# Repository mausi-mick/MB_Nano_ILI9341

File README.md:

.
    Test Board für Arduino „NANOs“ mit ILI9341, ILI9488-bzw. ST7735 SPI-Display

Bei vielen meiner Projekte  verwende ich den Arduino NANO oder Pin-kompatible Prozessoren mit dem TFT-Farb-Display ILI9341 bzw. ILI9488 bzw. ST7735 aus folgenden Gründen:
  
    • Existenz vieler Bibliotheken (libs) mit zahlreichen Beispielen für Prozessor und Display
    • kompaktes Board mit relativ grosser Anzahl herausgeführter Pins für andere Funktionen,
    • leicht beschaffbar / preisgünstig
    • Existenz von „NANO“  Boards mit anderem Processor mit NANO-“Pin-mapping“
    • mit HW-SPI ist das Display -auch am NANO – relativ schnell
    • die SPI-Displays ILI9341, ILI9488 und ST7735 haben gleiche/ähnliche Pinbelegung 
    • unterschiedliche Displaygrössen (1.8“,2,4“,2.8“,3.2“.3.5“,4“) (mit/ohne Touch) erhältlich
    • unterschiedliche Auflösungen (128x160), (240x320), (320x 400)

mittlerweile sind zum Arduino-NANO pinkompatible Boards erhältlich, z.B. :
  
    • LGT8F328P----»Mini EVB Nano style“, Prozessor: modifzierter ATMega328
    • Arduino EVERY:                                     Prozessor: ATMega4809
    • Arduino NANO ESP32                           ,Prozessor: ESP32
    • Arduino NANO 33 BLE                         ,Prozessor: nRF52840
    • Arduino NANO 33 IOT                         , Prozessor: M0+SAMD21
    • Arduino NANO RP2040 Connect          ,Prozessor: RP2040

Die neueren Boards sind dann eher auf 3,3 V Logik ausgerichtet bzw. z.T. umlötbar.

Als Entwickler möchte ich eigentlich möglichst schnell zur Anwendung kommen und mich nicht 
mit den Logik-Leveln rumschlagen , sondern den Prozessor und das Display auf ein
Board setzen und mit der Entwicklung loslegen., möglichst ohne viele Leitugen zu verlegen. 

Daher habe ich dieses Board entwickelt, auf dem Steckfassungen für das Display und das „NANO“-Board angeordnet sind und zusätzlich noch Steck Buchsen für:
    • einen DUAL-DAC MCP48x2
    • bis zu vier Drehencoder ( bzw. Potis),
    • vier Drucktaster
    • vier LED Anzeigen
    • ein Mini-Breadboard 
    • negative Sapnnungsquelle(-5V / ca 100mA) für Oper.verstärker

Das SPI-Display ( ILI9341, ILI9488, ST7735) wird direkt auf das Board gesteckt , auf dem sich die Verdrahtung für die Spannungsversorgung und die SPI-Anschlüsse (CS (Chipselect) an D10, DC (Data/Control) an D9)  des Displays befindet. Die Touch Pins und die SD-Karten Pins des Displays sind auf Buchsenleisten herausgeführt, ebenso wie alle Prozessor-Pins.

Es sind Displays in den Grössen 1.8“(ST7735), 2.4, 2.8 , 3.2“ (ILI9341) bzw. 3.5, 4.0“ (ILI9488) verwendbar.

Alles ist auf einer einlagigen Platine im Europa-Format (160x100) untergebracht.
Die Stromversorgung des Boards und die Programmierung erfolgt vom PC / Notebook über ein USB-Kabel, der Strom ist mit  500 mA abgesichert.
Ist die Programmierung abgeschlossen, kann das Board auch über eine USB Powerbank betrieben werden.

Nur für grössere Verbraucher (Servos, Motoren, Relais,…) wird eine zusätzliche entsprechend
dimensionierte Spannungsversorgung benötigt.

Von diesem „Main“ Board sind die „NANO“ Boards zur Programmierung über kurze USB Kabel verbunden, je nach Board mit Mini-USB (NANO), Micro-USB (Arduino EVERY, LTG8F328) oder
USB-C (LGT8F328 (blaue Platine),.

Zu dem Board gibt es KiCad-files (KiCad 7.0) und ein Blockdiagramm (DrawIO), auch als pdf.

Ausserdem gibt es noch zwei Adapter-Platinen für
den  
            Adafruit-Metro Mini 328
   
und den

            Raspberry PICO RP2040 (W) 
  Ausserdem werden Testprogramme zu den einzelnen Boards und Displays beigefügt.

   Hardware-Komponenten

hier sind jetzt nur die wesentlichen Komponenten / Module aufgeführt, die Details kann man den KiCad Stücklisten entnehmen.

    • ILI9341 SPI-Display (2.4“, 2.8“ oder 3.2“) (Touch bzw ohne Touch) (240x320 Pixel)
    • bzw ILI9488 Display (3,5“ bzw. 4.0“)  (Touch bzw ohne Touch) (320x400 Pixel)
    • bzw. ST7735 Display( 1.8“)  ohne Touch (128x160 Pixel)
    • Arduino NANO  oder Varianten gleicher Pin-Belegung 
    • USB C Buchse zur Verbindung PC/Notebbok
    • USB-A-Buchsezur Verbindung zum Prozesorboard
    • je nach Prozessorboard kurzes USB-Kabel mit mini-, micro USB-Stecker / USB-C-Stecker
    • diverse Buchsenleisten Raster 2.54 mm
    • LDO variabel ( MC33269) für 3.7V aus 5V
    • Schiebeschalter/Kippscahlter 1x UM)
    • diverse Widerstände, Kondenatoren ,  Dioden und Sicherungen
    • optional:
    •    DualDAC MCPM4802, MCP4812, MCP4822 ( 8, 10,12 bit SPI 
    •    1x DIL8-Fassung
    •    4xButtonSwitch
    •    4xLeds
    •    Dreh-Encoder (0-4 Stück)  ??
    •    Mini-Bread-Board
    •    -negatve Spannungsverorgung mit ICL7662 Modul
    •   Adapterboards für Adafruit Metro-Mini 328 / Raspberry PI RP2040

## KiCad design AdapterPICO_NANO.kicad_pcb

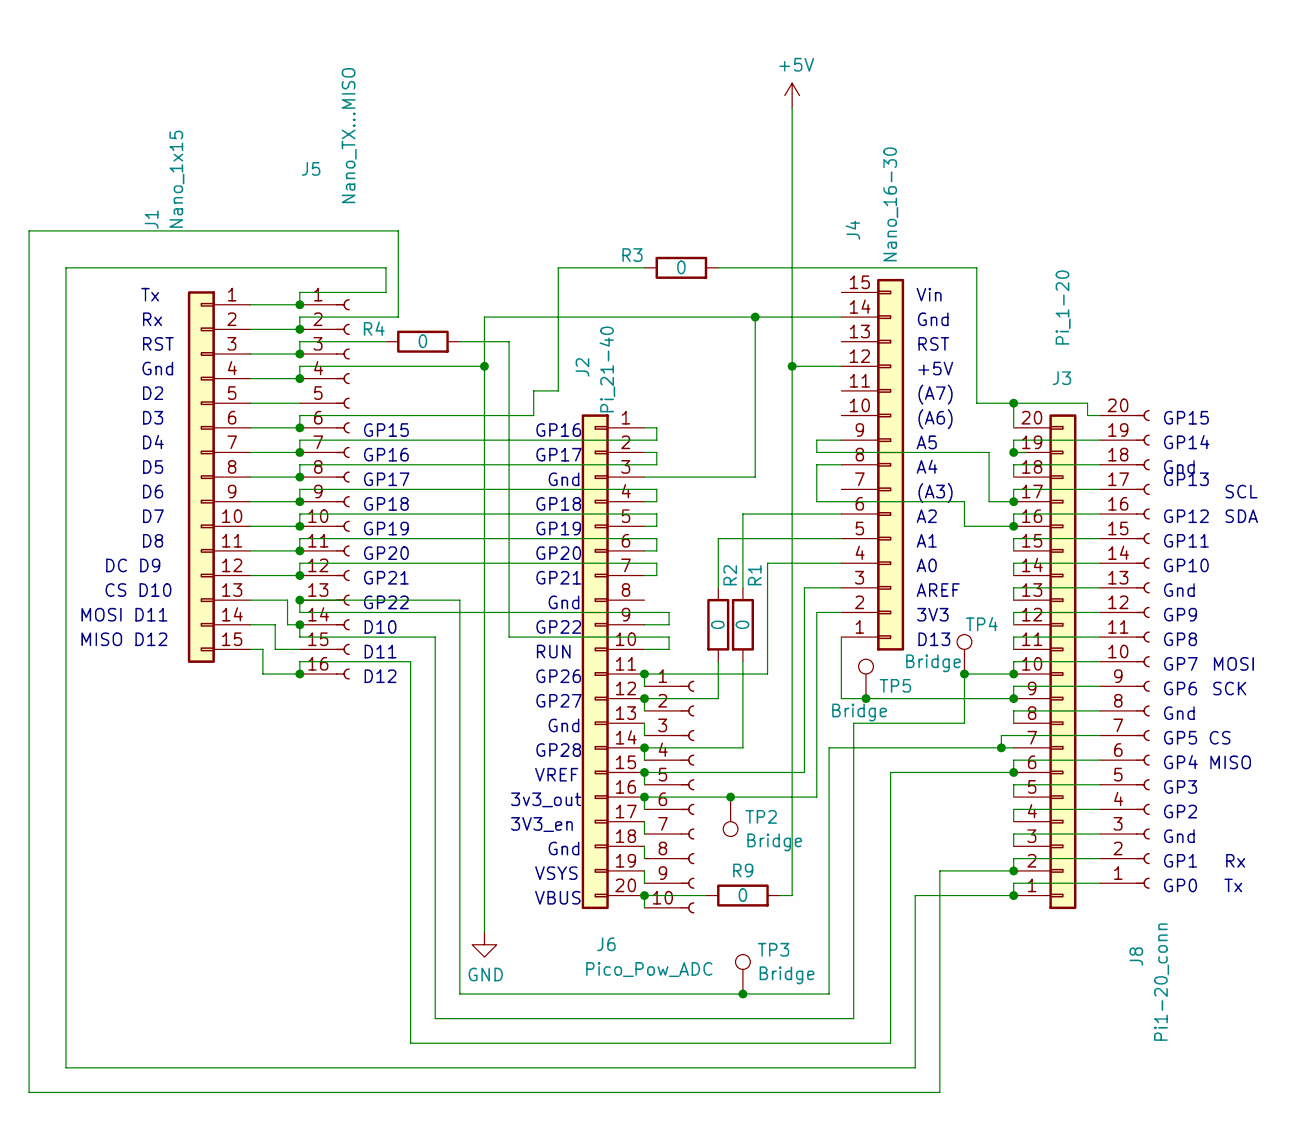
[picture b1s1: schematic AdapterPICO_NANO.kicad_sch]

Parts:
J1: Nano_1x15; PinHeader_1x15_P2.54mm_Vertical
J2: Pi_21-40; PinSocket_1x20_P2.54mm_Vertical
J3: Pi_1-20; PinSocket_1x20_P2.54mm_Vertical
J4: Nano_16-30; PinHeader_1x15_P2.54mm_Vertical
J5: Nano_TX...MISO; PinSocket_1x16_P2.54mm_Vertical
J6: Pico_Pow_ADC; PinSocket_1x10_P2.54mm_Vertical
J8: Pi1-20_conn; PinSocket_1x20_P2.54mm_Vertical
R1, R2, R3: 0; R_Axial_DIN0204_L3.6mm_D1.6mm_P7.62mm_Horizontal
R4: 0; R_Axial_DIN0207_L6.3mm_D2.5mm_P15.24mm_Horizontal
R9: 0; R_Axial_DIN0207_L6.3mm_D2.5mm_P10.16mm_Horizontal
TP2, TP3, TP4, TP5: Bridge; TestPoint_Bridge_Pitch5.08mm_Drill0.7mm

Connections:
+5V: J4.12, R9.2
GND: J1.4, J2.3, J4.14, J5.4
unnamed: J1.1, J3.1, J5.1, J8.1
unnamed: J1.2, J3.2, J5.2, J8.2
unnamed: J1.3, J5.3, R4.1
unnamed: J1.5, J5.5
unnamed: J1.6, J5.6, R3.1
unnamed: J1.7, J2.1, J5.7
unnamed: J1.8, J2.2, J5.8
unnamed: J1.9, J2.4, J5.9
unnamed: J1.10, J2.5, J5.10
unnamed: J1.11, J2.6, J5.11
unnamed: J1.12, J2.7, J5.12
unnamed: J1.13, J3.10, J5.14, J8.10, TP4.1
unnamed: J1.14, J5.15
unnamed: J1.15, J3.6, J5.16, J8.6
unnamed: J2.9, J3.7, J5.13, J8.7, TP3.1
unnamed: J2.10, R4.2
unnamed: J2.11, J4.4, J6.1
unnamed: J2.12, J6.2, R2.2
unnamed: J2.13, J6.3
unnamed: J2.14, J6.4, R1.2
unnamed: J2.15, J4.3, J6.5
unnamed: J2.16, J4.2, J6.6, TP2.1
unnamed: J2.17, J6.7
unnamed: J2.18, J6.8
unnamed: J2.19, J6.9
unnamed: J2.20, J6.10, R9.1
unnamed: J3.3, J8.3
unnamed: J3.4, J8.4
unnamed: J3.5, J8.5
unnamed: J3.8, J8.8
unnamed: J3.9, J4.1, J8.9, TP5.1
unnamed: J3.11, J8.11
unnamed: J3.12, J8.12
unnamed: J3.13, J8.13
unnamed: J3.14, J8.14
unnamed: J3.15, J8.15
unnamed: J3.16, J4.8, J8.16
unnamed: J3.17, J4.9, J8.17
unnamed: J3.18, J8.18
unnamed: J3.19, J8.19
unnamed: J3.20, J8.20, R3.2
unnamed: J4.5, R2.1
unnamed: J4.6, R1.1

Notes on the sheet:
D10
Vin
GP26
SDA
GP16
GP12
GP13
RST
GP9
VBUS
GP5 CS
CS D10
SCL
MOSI
GP20
GP7
3V3
DC D9
Gnd
GP15
GP3
(A6)
MISO D12
GP19
GP27
GP18
VSYS
D11
GP21
GP14
D12
SCK
(A3)
GP11
AREF
GP17
GP28
GP0
MOSI D11
RUN

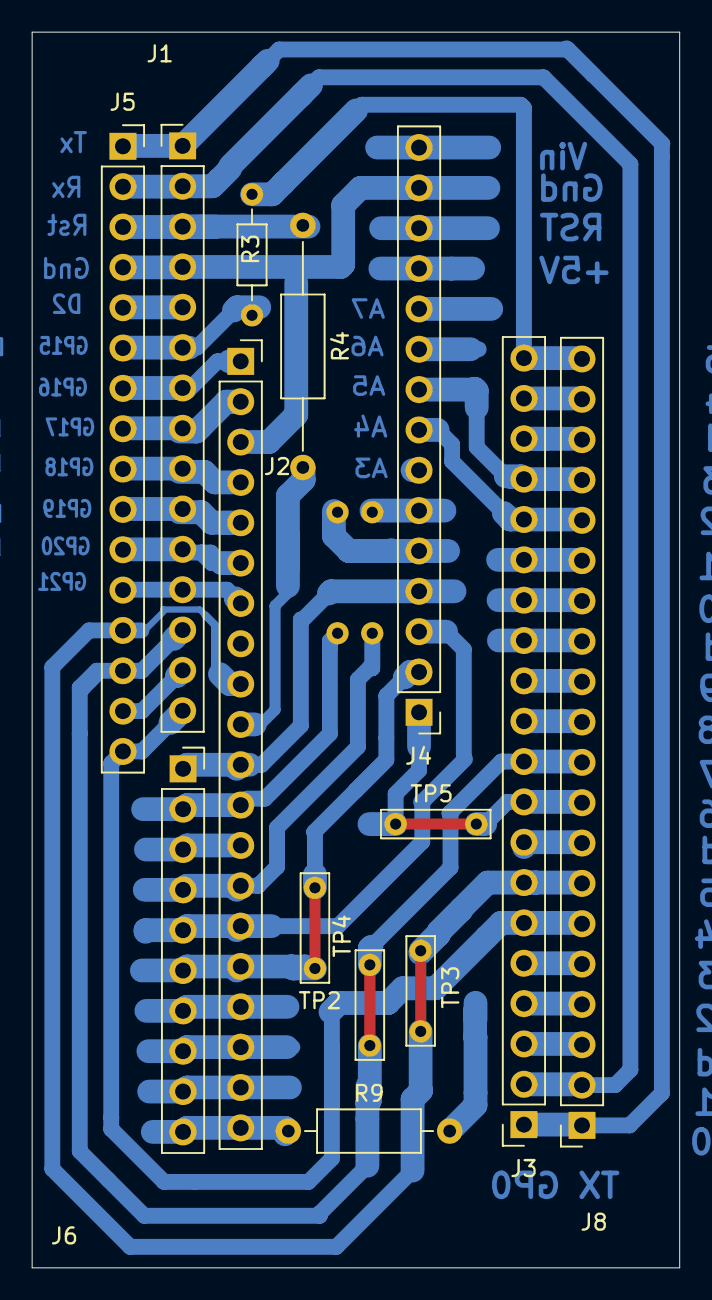
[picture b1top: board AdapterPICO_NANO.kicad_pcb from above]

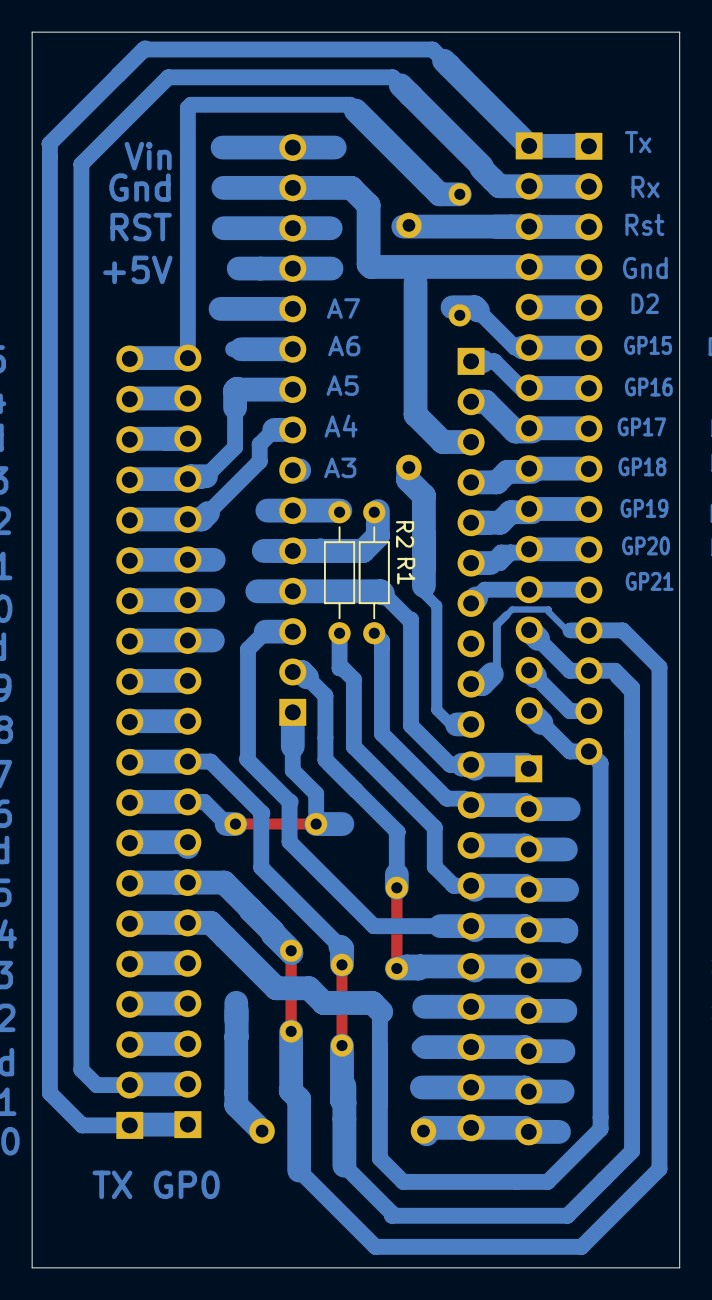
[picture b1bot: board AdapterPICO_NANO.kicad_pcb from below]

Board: 2 copper layers, 40.8 x 77.8 mm, 16 parts (2 on the bottom side), 45 nets.

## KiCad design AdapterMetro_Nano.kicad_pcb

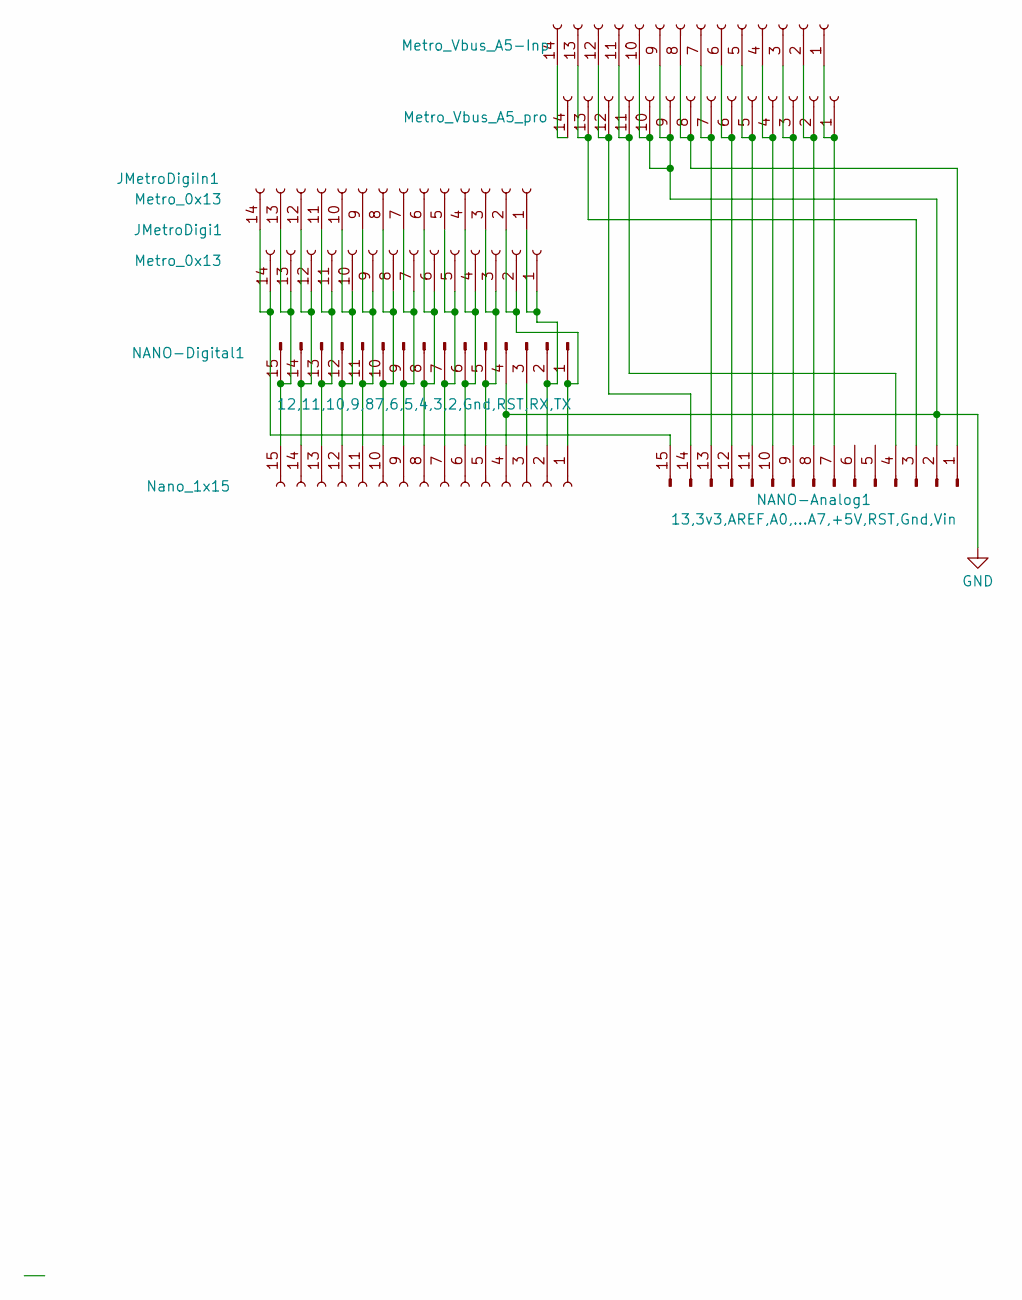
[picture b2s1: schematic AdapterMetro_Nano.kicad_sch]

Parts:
JMetroAna1: Metro_Vbus_A5-Inp; PinSocket_1x14_P2.54mm_Vertical
JMetroAna2: Metro_Vbus_A5_pro; PinSocket_1x14_P2.54mm_Vertical
JMetroDigi1: Metro_0x13; PinSocket_1x14_P2.54mm_Vertical
JMetroDigiIn1: Metro_0x13; PinSocket_1x14_P2.54mm_Vertical
JNanoDigi2: Nano_1x15; PinSocket_1x15_P2.54mm_Vertical
NANO-Analog1: 13,3v3,AREF,A0,...A7,+5V,RST,Gnd,Vin; PinHeader_1x15_P2.54mm_Vertical
NANO-Digital1: 12,11,10,9,87,6,5,4,3,2,Gnd,RST,RX,TX; PinHeader_1x15_P2.54mm_Vertical

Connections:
GND: JMetroAna1.9, JMetroAna1.10, JMetroAna2.9, JMetroAna2.10, JNanoDigi2.4, NANO-Analog1.2, NANO-Digital1.4
unnamed: JMetroAna1.1, JMetroAna2.1, NANO-Analog1.7
unnamed: JMetroAna1.2, JMetroAna2.2, NANO-Analog1.8
unnamed: JMetroAna1.3, JMetroAna2.3, NANO-Analog1.9
unnamed: JMetroAna1.4, JMetroAna2.4, NANO-Analog1.10
unnamed: JMetroAna1.5, JMetroAna2.5, NANO-Analog1.11
unnamed: JMetroAna1.6, JMetroAna2.6, NANO-Analog1.12
unnamed: JMetroAna1.7, JMetroAna2.7, NANO-Analog1.13
unnamed: JMetroAna1.8, JMetroAna2.8, NANO-Analog1.1
unnamed: JMetroAna1.11, JMetroAna2.11, NANO-Analog1.4
unnamed: JMetroAna1.12, JMetroAna2.12, NANO-Analog1.14
unnamed: JMetroAna1.13, JMetroAna2.13, NANO-Analog1.3
unnamed: JMetroAna1.14, JMetroAna2.14
unnamed: JMetroDigi1.1, JMetroDigiIn1.1, JNanoDigi2.2, NANO-Digital1.2
unnamed: JMetroDigi1.2, JMetroDigiIn1.2, JNanoDigi2.1, NANO-Digital1.1
unnamed: JMetroDigi1.3, JMetroDigiIn1.3, JNanoDigi2.5, NANO-Digital1.5
unnamed: JMetroDigi1.4, JMetroDigiIn1.4, JNanoDigi2.6, NANO-Digital1.6
unnamed: JMetroDigi1.5, JMetroDigiIn1.5, JNanoDigi2.7, NANO-Digital1.7
unnamed: JMetroDigi1.6, JMetroDigiIn1.6, JNanoDigi2.8, NANO-Digital1.8
unnamed: JMetroDigi1.7, JMetroDigiIn1.7, JNanoDigi2.9, NANO-Digital1.9
unnamed: JMetroDigi1.8, JMetroDigiIn1.8, JNanoDigi2.10, NANO-Digital1.10
unnamed: JMetroDigi1.9, JMetroDigiIn1.9, JNanoDigi2.11, NANO-Digital1.11
unnamed: JMetroDigi1.10, JMetroDigiIn1.10, JNanoDigi2.12, NANO-Digital1.12
unnamed: JMetroDigi1.11, JMetroDigiIn1.11, JNanoDigi2.13, NANO-Digital1.13
unnamed: JMetroDigi1.12, JMetroDigiIn1.12, JNanoDigi2.14, NANO-Digital1.14
unnamed: JMetroDigi1.13, JMetroDigiIn1.13, JNanoDigi2.15, NANO-Digital1.15
unnamed: JMetroDigi1.14, JMetroDigiIn1.14, NANO-Analog1.15
unnamed: JNanoDigi2.3, NANO-Digital1.3

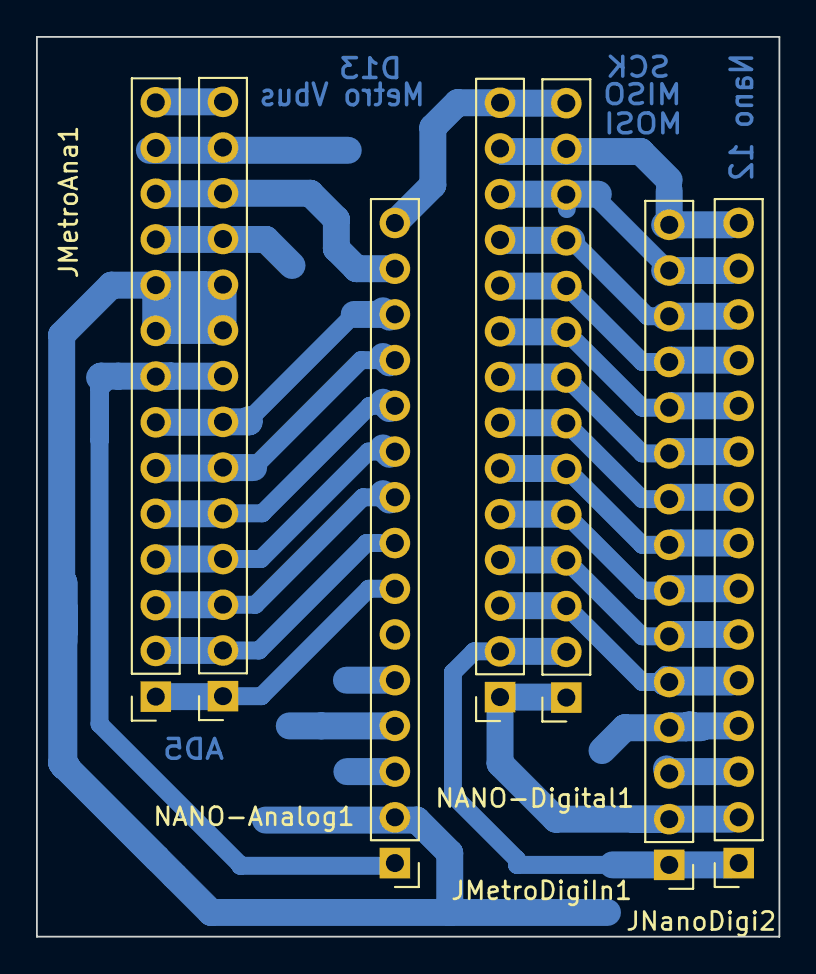
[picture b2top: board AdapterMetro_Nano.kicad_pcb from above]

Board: 2 copper layers, 41.2 x 50.0 mm, 7 parts (0 on the bottom side), 28 nets.

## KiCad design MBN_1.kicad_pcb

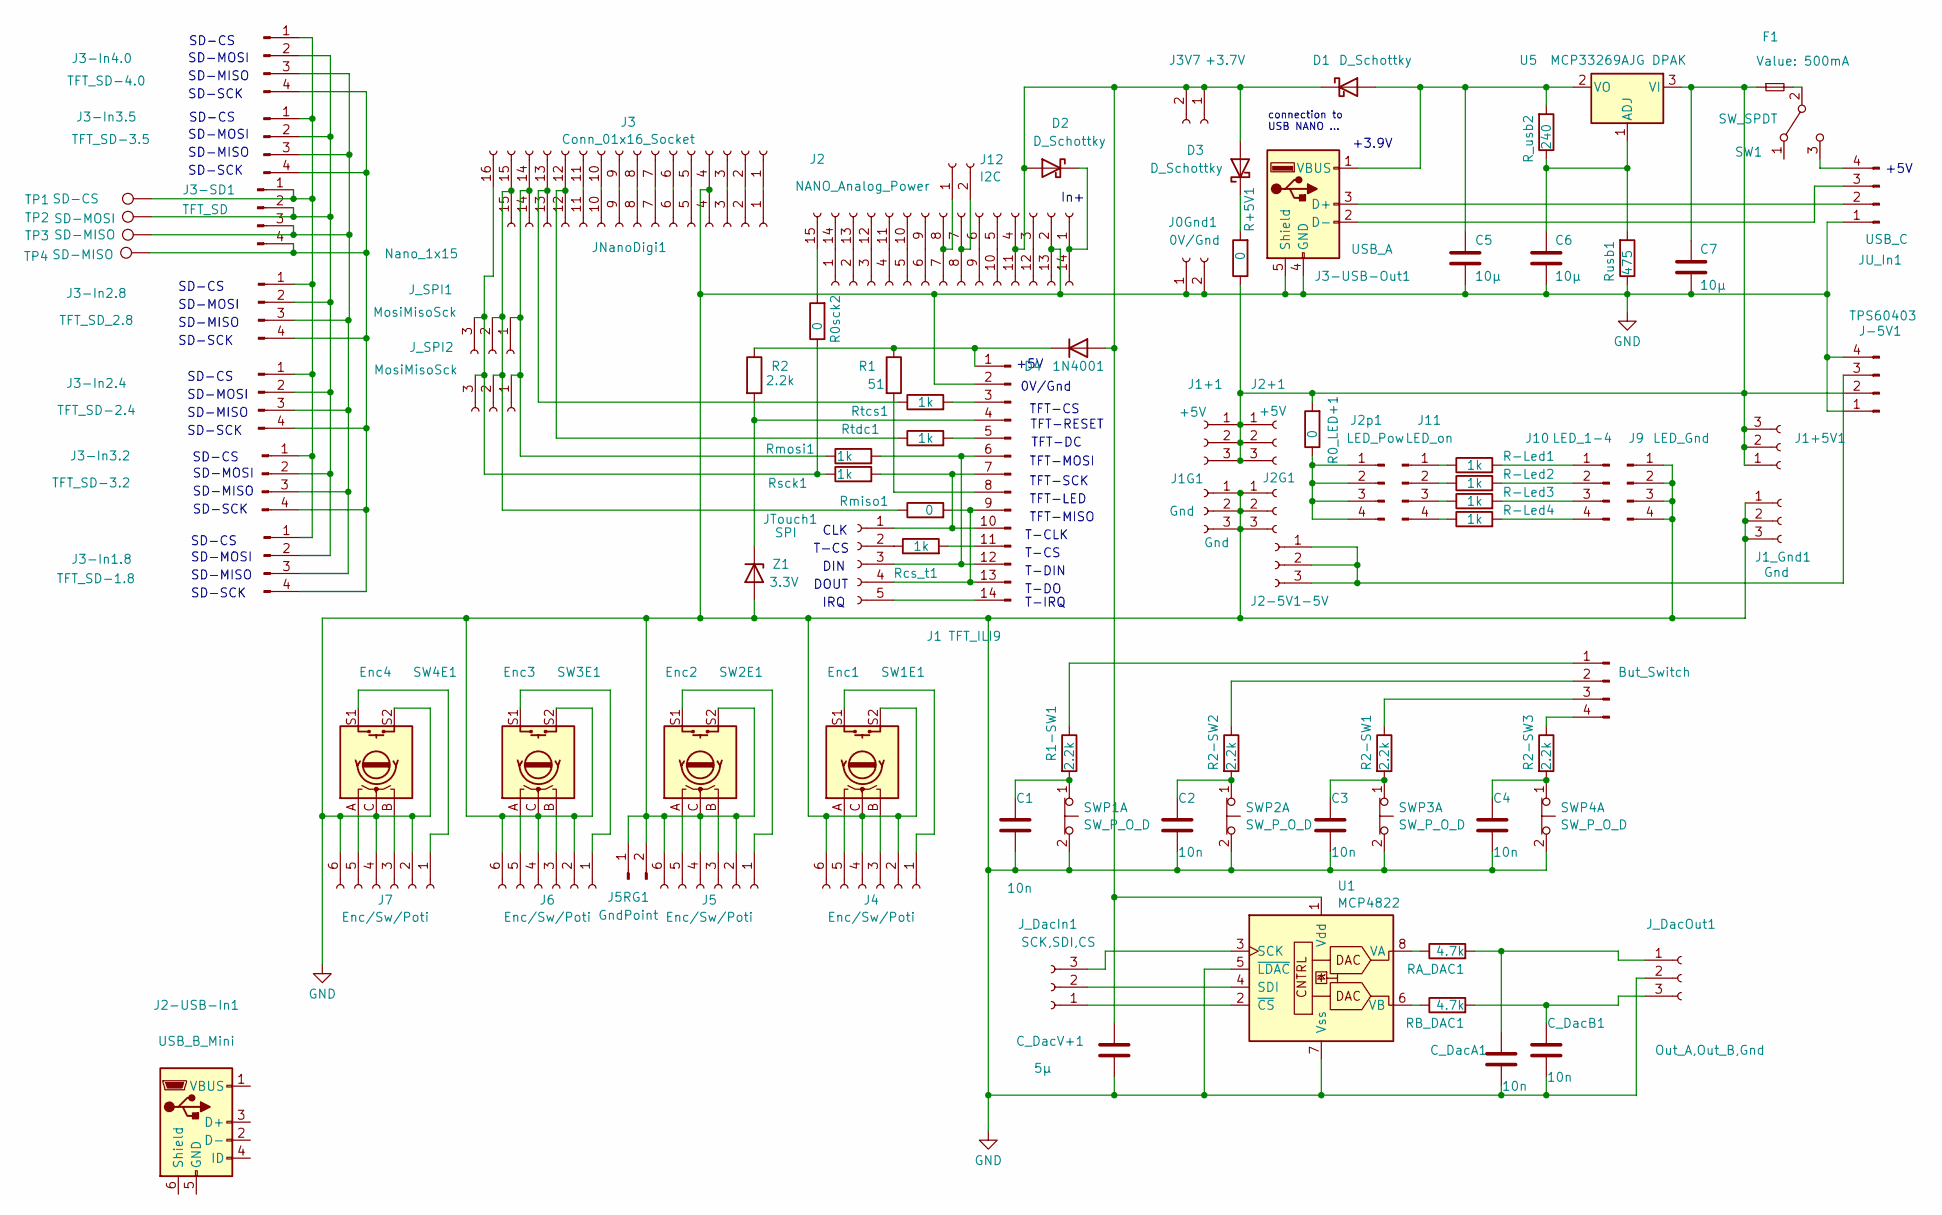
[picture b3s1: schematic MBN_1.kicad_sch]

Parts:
C1, C2, C3, C4: 10n; C_1206_3216Metric_Pad1.33x1.80mm_HandSolder
C5, C6, C7: 10µ; C_1812_4532Metric_Pad1.57x3.40mm_HandSolder
C_DacA1: 10n; C_1206_3216Metric_Pad1.33x1.80mm_HandSolder
C_DacB1: 10n; C_1206_3216Metric_Pad1.33x1.80mm_HandSolder
C_DacV+1: 5µ; C_1812_4532Metric_Pad1.57x3.40mm_HandSolder
D1: D_Schottky; D_DO-15_P15.24mm_Horizontal
D2: D_Schottky; D_2010_5025Metric_Pad1.52x2.65mm_HandSolder
D3: D_Schottky; D_DO-15_P12.70mm_Horizontal
D4: 1N4001; D_2010_5025Metric_Pad1.52x2.65mm_HandSolder
F1: 500mA; Fuse_2010_5025Metric_Pad1.52x2.65mm_HandSolder
J0Gnd1: 0V/Gnd; PinHeader_1x02_P2.54mm_Vertical
J1: TFT_ILI9; PinHeader_1x14_P2.54mm_Vertical
J1+1, J1+5V1, J2+1: +5V; PinHeader_1x03_P2.54mm_Vertical
J1G1, J1_Gnd1, J2G1: Gnd; PinHeader_1x03_P2.54mm_Vertical
J2: NANO_Analog_Power; PinHeader_1x14_P2.54mm_Vertical
J2-5V1: -5V; PinHeader_1x03_P2.54mm_Vertical
J2-USB-In1: USB_B_Mini; USB_Mini-B_Wuerth_65100516121_Horizontal
J2p1: LED_Pow; PinHeader_1x04_P2.54mm_Vertical
J3: Conn_01x16_Socket; PinHeader_1x16_P2.54mm_Vertical
J3-In1.8: TFT_SD-1.8; PinHeader_1x04_P2.54mm_Vertical
J3-In2.4: TFT_SD-2.4; PinHeader_1x04_P2.54mm_Vertical
J3-In2.8: TFT_SD_2.8; PinSocket_1x04_P2.54mm_Vertical
J3-In3.2: TFT_SD-3.2; PinHeader_1x04_P2.54mm_Vertical
J3-In3.5: TFT_SD-3.5; PinHeader_1x04_P2.54mm_Vertical
J3-In4.0: TFT_SD-4.0; PinHeader_1x04_P2.54mm_Vertical
J3-SD1: TFT_SD; PinHeader_1x04_P2.54mm_Horizontal
J3-USB-Out1: USB_A; USB_A_Stewart_SS-52100-001_Horizontal
J3V7: +3.7V; PinHeader_1x02_P2.54mm_Vertical
J4, J5, J6, J7: Enc/Sw/Poti; PinHeader_1x06_P2.54mm_Vertical
J5RG1: GndPoint; PinHeader_1x02_P2.54mm_Vertical
J8: But_Switch; PinHeader_1x04_P2.54mm_Vertical
J9: LED_Gnd; PinHeader_1x04_P2.54mm_Vertical
J10: LED_1-4; PinHeader_1x04_P2.54mm_Vertical
J11: LED_on; PinHeader_1x04_P2.54mm_Vertical
J12: I2C; PinHeader_1x02_P2.54mm_Vertical
J-5V1: TPS60403; PinHeader_1x04_P2.54mm_Vertical
JNanoAnal_1_15: +InGnd...; PinSocket_1x15_P2.54mm_Vertical
JNanoDigi1: Nano_1x15; PinSocket_1x15_P2.54mm_Vertical
JTouch1: SPI; PinHeader_1x05_P2.54mm_Vertical
JU_In1: USB_C; PinHeader_1x04_P2.54mm_Vertical
J_DacIn1: SCK,SDI,CS; PinHeader_1x03_P2.54mm_Vertical
J_DacOut1: Out_A,Out_B,Gnd; PinHeader_1x03_P2.54mm_Vertical
J_SPI1, J_SPI2: MosiMisoSck; PinHeader_1x03_P2.54mm_Vertical
R0_LED+1, R0sck2: 0; R_Axial_DIN0207_L6.3mm_D2.5mm_P15.24mm_Horizontal
R1: 51; R_Axial_DIN0309_L9.0mm_D3.2mm_P20.32mm_Horizontal
R1-SW1, R2-SW1, R2-SW2, R2-SW3: 2.2k; R_1206_3216Metric_Pad1.30x1.75mm_HandSolder
R2: 2.2k; R_Axial_DIN0207_L6.3mm_D2.5mm_P10.16mm_Horizontal
R+5V1: 0; R_Axial_DIN0207_L6.3mm_D2.5mm_P10.16mm_Horizontal
R-Led1, R-Led2, R-Led3, R-Led4: 1k; R_1206_3216Metric_Pad1.30x1.75mm_HandSolder
RA_DAC1: 4.7k; R_1206_3216Metric_Pad1.30x1.75mm_HandSolder
RB_DAC1: 4.7k; R_1206_3216Metric_Pad1.30x1.75mm_HandSolder
R_usb2: 240; R_Axial_DIN0207_L6.3mm_D2.5mm_P10.16mm_Horizontal
Rcs_t1: 1k; R_0805_2012Metric_Pad1.20x1.40mm_HandSolder
Rmiso1: 0; R_Axial_DIN0207_L6.3mm_D2.5mm_P10.16mm_Horizontal
Rmosi1: 1k; R_Axial_DIN0204_L3.6mm_D1.6mm_P7.62mm_Horizontal
Rsck1: 1k; R_Axial_DIN0207_L6.3mm_D2.5mm_P15.24mm_Horizontal
Rtcs1: 1k; R_0805_2012Metric_Pad1.20x1.40mm_HandSolder
Rtdc1: 1k; R_0805_2012Metric_Pad1.20x1.40mm_HandSolder
Rusb1: 475; R_Axial_DIN0207_L6.3mm_D2.5mm_P10.16mm_Horizontal
SW1: SW_SPDT; Molex_KK-396_5273-03A_1x03_P3.96mm_Vertical
SW1E1: Enc1; RotaryEncoder_Alps_EC11E-Switch_Vertical_H20mm
SW2E1: Enc2; RotaryEncoder_Alps_EC11E-Switch_Vertical_H20mm
SW3E1: Enc3; RotaryEncoder_Alps_EC11E-Switch_Vertical_H20mm
SW4E1: Enc4; RotaryEncoder_Alps_EC11E-Switch_Vertical_H20mm
SWP1, SWP2, SWP3, SWP4: SW_P_O_D; SW_PUSH_6mm_H7.3mm
TP1: SD-CS; TestPoint_Keystone_5000-5004_Miniature
TP2: SD-MOSI; TestPoint_Keystone_5000-5004_Miniature
TP3, TP4: SD-MISO; TestPoint_Keystone_5000-5004_Miniature
U1: MCP4822; DIP-8_W7.62mm_LongPads
U5: MCP33269AJG DPAK; ATPAK-2
Z1: 3.3V; D_DO-41_SOD81_P7.62mm_Horizontal

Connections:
GND: C1.2, C2.2, C3.2, C4.2, C5.2, C6.2, C7.2, C_DacA1.2, C_DacB1.2, C_DacV+1.2, J0Gnd1.1, J0Gnd1.2, J1.2, J1G1.1, J1G1.2, J1G1.3, J1_Gnd1.1, J1_Gnd1.2, J1_Gnd1.3, J2.13, J2G1.1, J2G1.2, J2G1.3, J3.4, J3-USB-Out1.4 (GND), J3-USB-Out1.5 (Shield), J4.2, J4.4, J4.6, J5.2, J5.4, J5.6, J5RG1.1, J5RG1.2, J6.2, J6.4, J6.6, J7.2, J7.4, J7.6, J9.1, J9.2, J9.3, J9.4, J-5V1.1, J-5V1.4, JNanoAnal_1_15.2, JNanoDigi1.4, JU_In1.1, J_DacOut1.2, Rusb1.1, SW1E1.C, SW1E1.S2, SW2E1.C, SW2E1.S2, SW3E1.C, SW3E1.S2, SW4E1.C, SW4E1.S2, SWP1.2, SWP2.2, SWP3.2, SWP4.2, U1.5 (~LDAC), U1.7 (Vss), Z1.2 (A)
unnamed: C1.1, R1-SW1.2, SWP1.1
unnamed: C2.1, R2-SW2.2, SWP2.1
unnamed: C3.1, R2-SW1.2, SWP3.1
unnamed: C4.1, R2-SW3.2, SWP4.1
unnamed: C5.1, D1.2 (A), J3-USB-Out1.1 (VBUS), R_usb2.2, U5.2 (VO)
unnamed: C_DacV+1.1, D1.1 (K), D2.2 (A), D3.2 (A), D4.2 (A), J2.11, J3V7.1, J3V7.2, JNanoAnal_1_15.4, U1.1 (Vdd)
unnamed: D2.1 (K), J2.14, JNanoAnal_1_15.1
unnamed: D3.1 (K), R+5V1.2
unnamed: D4.1 (K), J1.1, R1.1, R2.1
unnamed: J1.3, Rtcs1.2
unnamed: J1.4, R2.2, Z1.1 (K)
unnamed: J1.5, Rtdc1.2
unnamed: J1.8, R1.2
unnamed: J1.7, J1.10, JTouch1.1, Rsck1.2
unnamed: J1.11, Rcs_t1.2
unnamed: J1.6, J1.12, JTouch1.3, Rmosi1.2
unnamed: J1.9, J1.13, JTouch1.4, Rmiso1.2
unnamed: J1.14, JTouch1.5
unnamed: J2.1, JNanoAnal_1_15.14
unnamed: J2.2, JNanoAnal_1_15.13
unnamed: J2.3, JNanoAnal_1_15.12
unnamed: J2.4, JNanoAnal_1_15.11
unnamed: J2.5, JNanoAnal_1_15.10
unnamed: J2.6, JNanoAnal_1_15.9
unnamed: J2.9, JNanoAnal_1_15.6
unnamed: J2.10, JNanoAnal_1_15.5
unnamed: J2.12, JNanoAnal_1_15.3
unnamed: J2p1.1, J2p1.2, J2p1.3, J2p1.4, R0_LED+1.1
unnamed: J3-In1.8.1, J3-In2.4.1, J3-In2.8.1, J3-In3.2.1, J3-In3.5.1, J3-In4.0.1, J3-SD1.1, TP1.1
unnamed: J3-In1.8.2, J3-In2.4.2, J3-In2.8.2, J3-In3.2.2, J3-In3.5.2, J3-In4.0.2, J3-SD1.2, TP2.1
unnamed: J3-In1.8.3, J3-In2.4.3, J3-In2.8.3, J3-In3.2.3, J3-In3.5.3, J3-In4.0.3, J3-SD1.3, TP3.1
unnamed: J3-In1.8.4, J3-In2.4.4, J3-In2.8.4, J3-In3.2.4, J3-In3.5.4, J3-In4.0.4, J3-SD1.4, TP4.1
unnamed: J3.1, JNanoDigi1.1
unnamed: J3.2, JNanoDigi1.2
unnamed: J3.3, JNanoDigi1.3
unnamed: J3.5, JNanoDigi1.5
unnamed: J3.6, JNanoDigi1.6
unnamed: J3.7, JNanoDigi1.7
unnamed: J3.8, JNanoDigi1.8
unnamed: J3.9, JNanoDigi1.9
unnamed: J3.10, JNanoDigi1.10
unnamed: J3.11, JNanoDigi1.11
unnamed: J3.12, JNanoDigi1.12, Rtdc1.1
unnamed: J3.13, JNanoDigi1.13, Rtcs1.1
unnamed: J3.14, JNanoDigi1.14, J_SPI1.1, J_SPI2.1, Rmosi1.1
unnamed: J3.15, JNanoDigi1.15, J_SPI1.2, J_SPI2.2, Rmiso1.1
unnamed: J3.16, J_SPI1.3, J_SPI2.3, R0sck2.1, Rsck1.1
unnamed: J3-USB-Out1.3 (D+), JU_In1.2
unnamed: J3-USB-Out1.2 (D-), JU_In1.3
unnamed: J4.1, SW1E1.S1
unnamed: J4.3, SW1E1.B
unnamed: J4.5, SW1E1.A
unnamed: J5.1, SW2E1.S1
unnamed: J5.3, SW2E1.B
unnamed: J5.5, SW2E1.A
unnamed: J6.1, SW3E1.S1
unnamed: J6.3, SW3E1.B
unnamed: J6.5, SW3E1.A
unnamed: J7.1, SW4E1.S1
unnamed: J7.3, SW4E1.B
unnamed: J7.5, SW4E1.A
unnamed: J8.1, R1-SW1.1
unnamed: J8.2, R2-SW2.1
unnamed: J8.3, R2-SW1.1
unnamed: J8.4, R2-SW3.1
unnamed: J10.1, R-Led1.2
unnamed: J10.2, R-Led2.2
unnamed: J10.3, R-Led3.2
unnamed: J10.4, R-Led4.2
unnamed: J11.1, R-Led1.1
unnamed: J11.2, R-Led2.1
unnamed: J11.3, R-Led3.1
unnamed: J11.4, R-Led4.1
unnamed: J2.7, J12.1, JNanoAnal_1_15.8
unnamed: J2.8, J12.2, JNanoAnal_1_15.7
unnamed: C7.1, F1.1, J1+1.1, J1+1.2, J1+1.3, J1+5V1.1, J1+5V1.2, J1+5V1.3, J2+1.1, J2+1.2, J2+1.3, J-5V1.2, R0_LED+1.2, R+5V1.1, U5.3 (VI)
unnamed: J2-5V1.1, J2-5V1.2, J2-5V1.3, J-5V1.3
unnamed: JNanoAnal_1_15.15, R0sck2.2
unnamed: JTouch1.2, Rcs_t1.1
unnamed: JU_In1.4, SW1.3 (C)
unnamed: J_DacIn1.1, U1.2 (~CS)
unnamed: J_DacIn1.2, U1.4 (SDI)
unnamed: J_DacIn1.3, U1.3 (SCK)
unnamed: C_DacA1.1, J_DacOut1.1, RA_DAC1.2
unnamed: C_DacB1.1, J_DacOut1.3, RB_DAC1.2
unnamed: F1.2, SW1.2 (B)
unnamed: RA_DAC1.1, U1.8 (VA)
unnamed: RB_DAC1.1, U1.6 (VB)
unnamed: C6.1, R_usb2.1, Rusb1.2, U5.1 (ADJ)

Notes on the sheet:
CLK
SD-CS
SD-MISO
SD-MOSI
0V/Gnd
DIN
DOUT
TFT-LED
T-CS
TFT-RESET
TFT-DC
TFT-CS
T-CLK
T-DIN
connection to USB NANO ...
+5V
IRQ
TFT-SCK
SD-SCK
TFT-MOSI
T-DO
T-IRQ
+3.9V
TFT-MISO
In+

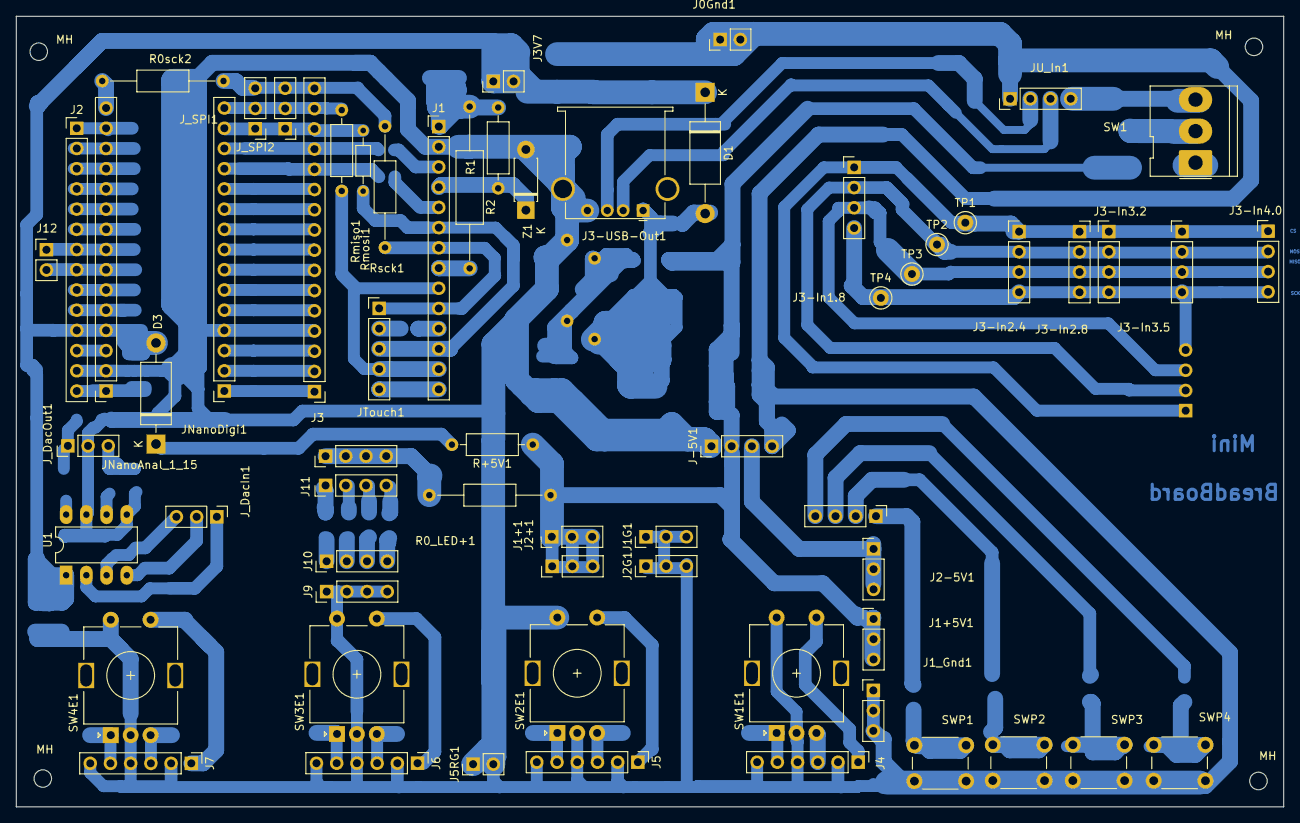
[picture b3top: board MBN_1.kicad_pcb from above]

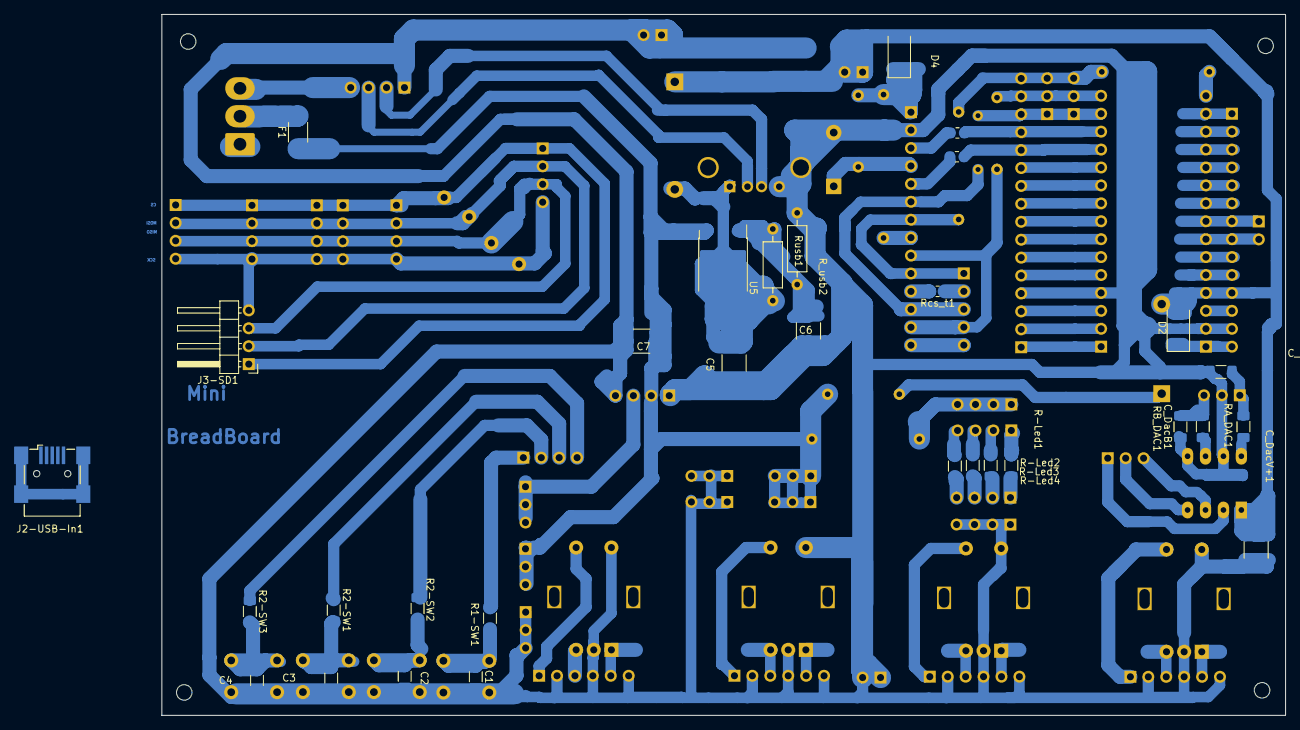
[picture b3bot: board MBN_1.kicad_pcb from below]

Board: 2 copper layers, 159.3 x 99.3 mm, 99 parts (31 on the bottom side), 90 nets.

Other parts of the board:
MH: MH_2.2; MountingHole_2.2mm_M2_DIN965
MH#2, MH#3, MH#4: MH_2.2; MountingHole_2.2mm_M2_DIN965

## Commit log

2023-12-09 Add files via upload
    .
    Test Board für Arduino „NANOs“ mit ILI9341, ILI9488-bzw. ST7735 SPI-Display
    Bei vielen meiner Projekte verwende ich den Arduino NANO oder Pin-kompatible Prozessoren mit dem TFT-Farb-Display ILI9341 bzw. ILI9488 bzw. ST7735 aus folgenden Gründen:
    • Existenz vieler Bibliotheken (libs) mit zahlreichen Beispielen für Prozessor und Display
    • kompaktes Board mit relativ grosser Anzahl herausgeführter Pins für andere Funktionen,
    • leicht beschaffbar / preisgünstig
2023-12-09 Update README.md
    .
    Test Board für Arduino „NANOs“ mit ILI9341, ILI9488-bzw. ST7735 SPI-Display
    Bei vielen meiner Projekte verwende ich den Arduino NANO oder Pin-kompatible Prozessoren mit dem TFT-Farb-Display ILI9341 bzw. ILI9488 bzw. ST7735 aus folgenden Gründen:
    • Existenz vieler Bibliotheken (libs) mit zahlreichen Beispielen für Prozessor und Display
    • kompaktes Board mit relativ grosser Anzahl herausgeführter Pins für andere Funktionen,
    • leicht beschaffbar / preisgünstig
2023-12-09 Update README.doc
    .
    Test Board für Arduino „NANOs“ mit ILI9341, ILI9488-bzw. ST7735 SPI-Display
    Bei vielen meiner Projekte verwende ich den Arduino NANO oder Pin-kompatible Prozessoren mit dem TFT-Farb-Display ILI9341 bzw. ILI9488 bzw. ST7735 aus folgenden Gründen:
    • Existenz vieler Bibliotheken (libs) mit zahlreichen Beispielen für Prozessor und Display
    • kompaktes Board mit relativ grosser Anzahl herausgeführter Pins für andere Funktionen,
    • leicht beschaffbar / preisgünstig
